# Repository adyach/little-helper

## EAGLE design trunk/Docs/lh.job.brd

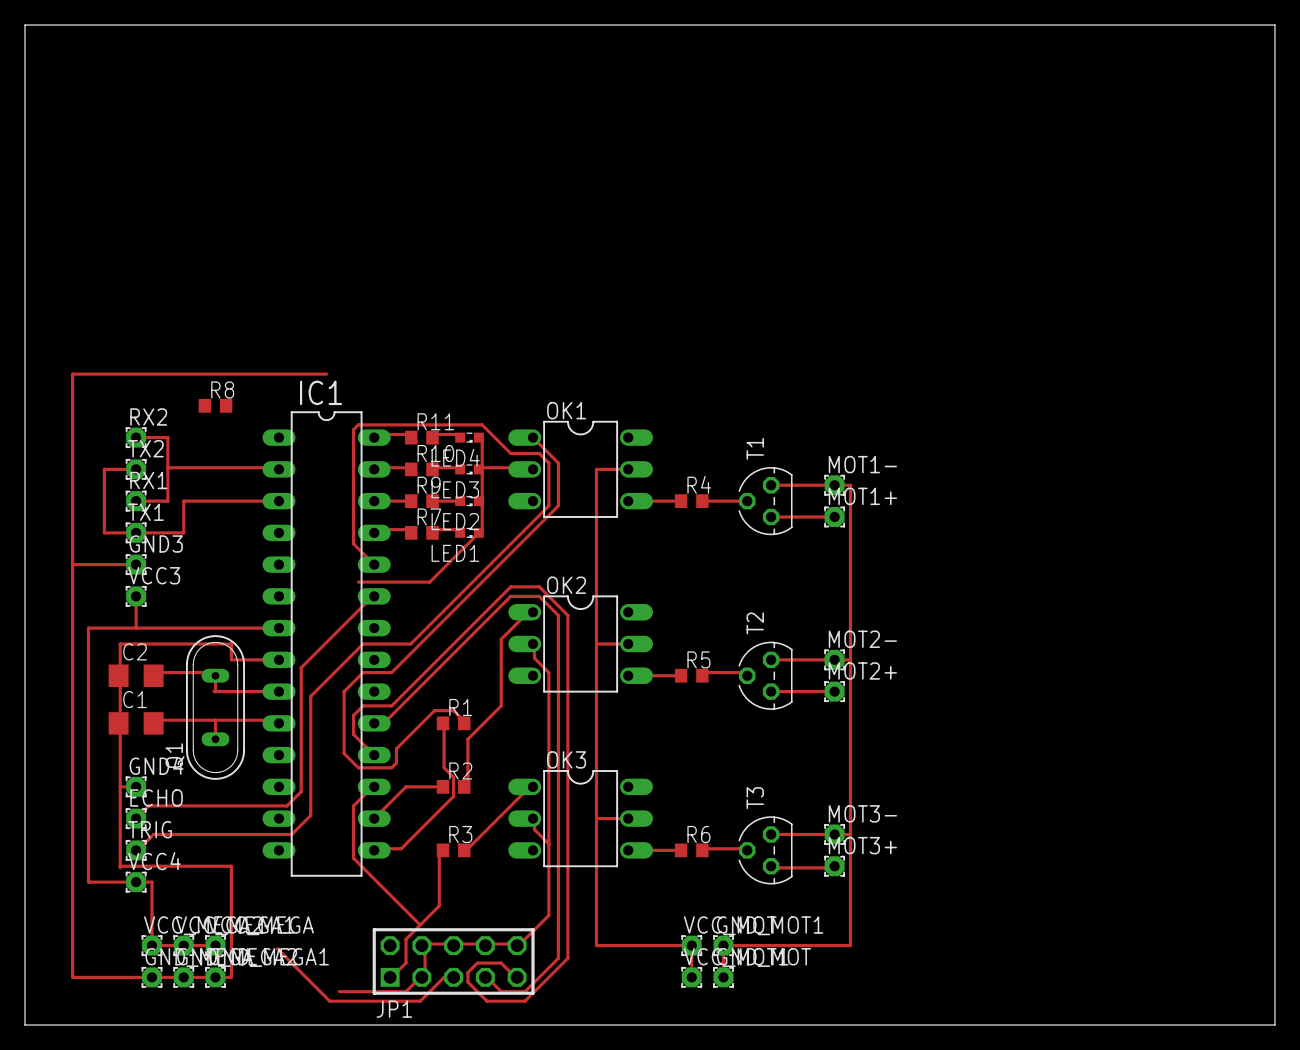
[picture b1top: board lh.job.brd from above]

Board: 2 copper layers, 100.0 x 80.0 mm, 52 parts (0 on the bottom side), 35 nets.

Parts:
C1, C2: C1206
ECHO: 1,6/0,8
GND3, GND4: 1,6/0,8
GND_MEGA, GND_MEGA1, GND_MEGA2: 1,6/0,8
GND_MOT, GND_MOT1: 1,6/0,8
IC1: MEGA8-P; DIL28-3
JP1: AVR-ISP-10
LED1, LED2, LED3, LED4: SML0603
MOT1+, MOT1-, MOT2+, MOT2-, MOT3+, MOT3-: 1,6/0,8
OK1, OK2, OK3: 4N35; DIL06
Q1: QS
R1: 200om; R0603
R2, R3: 200Om; R0603
R4, R5, R6: 1K; R0603
R7, R9, R10, R11: R0603
R8: 10K; R0603
RX1, RX2: 1,6/0,8
T1, T2, T3: 2N3904; TO92
TRIG: 1,6/0,8
TX1, TX2: 1,6/0,8
VCC3, VCC4: 1,6/0,8
VCC_MEGA, VCC_MEGA1, VCC_MEGA2: 1,6/0,8
VCC_MOT, VCC_MOT1: 1,6/0,8

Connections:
unnamed: IC1.15, R1.1
unnamed: IC1.16, R2.1
unnamed: IC1.17, JP1.1, R3.1
unnamed: OK1.1, R1.2
unnamed: OK2.1, R2.2
unnamed: OK3.1, R3.2
unnamed: OK1.4, R4.1
unnamed: R6.2, T3.2
unnamed: IC1.25, R7.1
unnamed: OK2.5, VCC_MOT.1, VCC_MOT1.1
unnamed: MOT1+.1, T1.3
unnamed: MOT2+.1, T2.3
unnamed: MOT3+.1, T3.3
unnamed: IC1.9, Q1.2
unnamed: C1.2, IC1.10, Q1.1
unnamed: IC1.19, JP1.7
unnamed: IC1.18, JP1.9
unnamed: R4.2, T1.2
unnamed: IC1.24, TRIG.1
unnamed: ECHO.1, IC1.23
unnamed: IC1.3, TX1.1, TX2.1
unnamed: R5.2, T2.2
unnamed: IC1.7, VCC3.1, VCC4.1, VCC_MEGA.1, VCC_MEGA1.1, VCC_MEGA2.1
unnamed: IC1.27, R10.1
unnamed: IC1.26, R9.1
unnamed: JP1.3, JP1.4, JP1.6, JP1.8, JP1.10, OK2.2, OK3.2
unnamed: IC1.28, R11.1
unnamed: LED1.A, R7.2
unnamed: LED2.A, R9.2
unnamed: LED3.A, R10.2
unnamed: LED4.A, R11.2
unnamed: GND_MOT.1, GND_MOT1.1, MOT1-.1, MOT3-.1, T1.1, T2.1, T3.1
S$2: LED1.C, LED2.C, LED3.C, LED4.C, OK1.2
S$6: RX1.1, RX2.1
S$7: C1.1, C2.1, GND3.1, GND4.1, GND_MEGA.1, GND_MEGA1.1, GND_MEGA2.1

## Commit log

2013-03-16 Initial directory structure.
2013-03-16 libs
2013-03-16 docs
2013-03-16 First release :)
2013-03-30 new plate with 4 sensors + new algorithm for processing the data from them.
2013-03-30 Mouse control. Fixed responses from controller.
2013-04-14 internal: removed logs
2014-05-01 New implementation.
2014-05-02 feature Client: bluetooth test.
2015-07-15 Migrating wiki contents from Google Code
2016-08-15 Imported from https://adyach@github.com/adyach/little-helper.git
